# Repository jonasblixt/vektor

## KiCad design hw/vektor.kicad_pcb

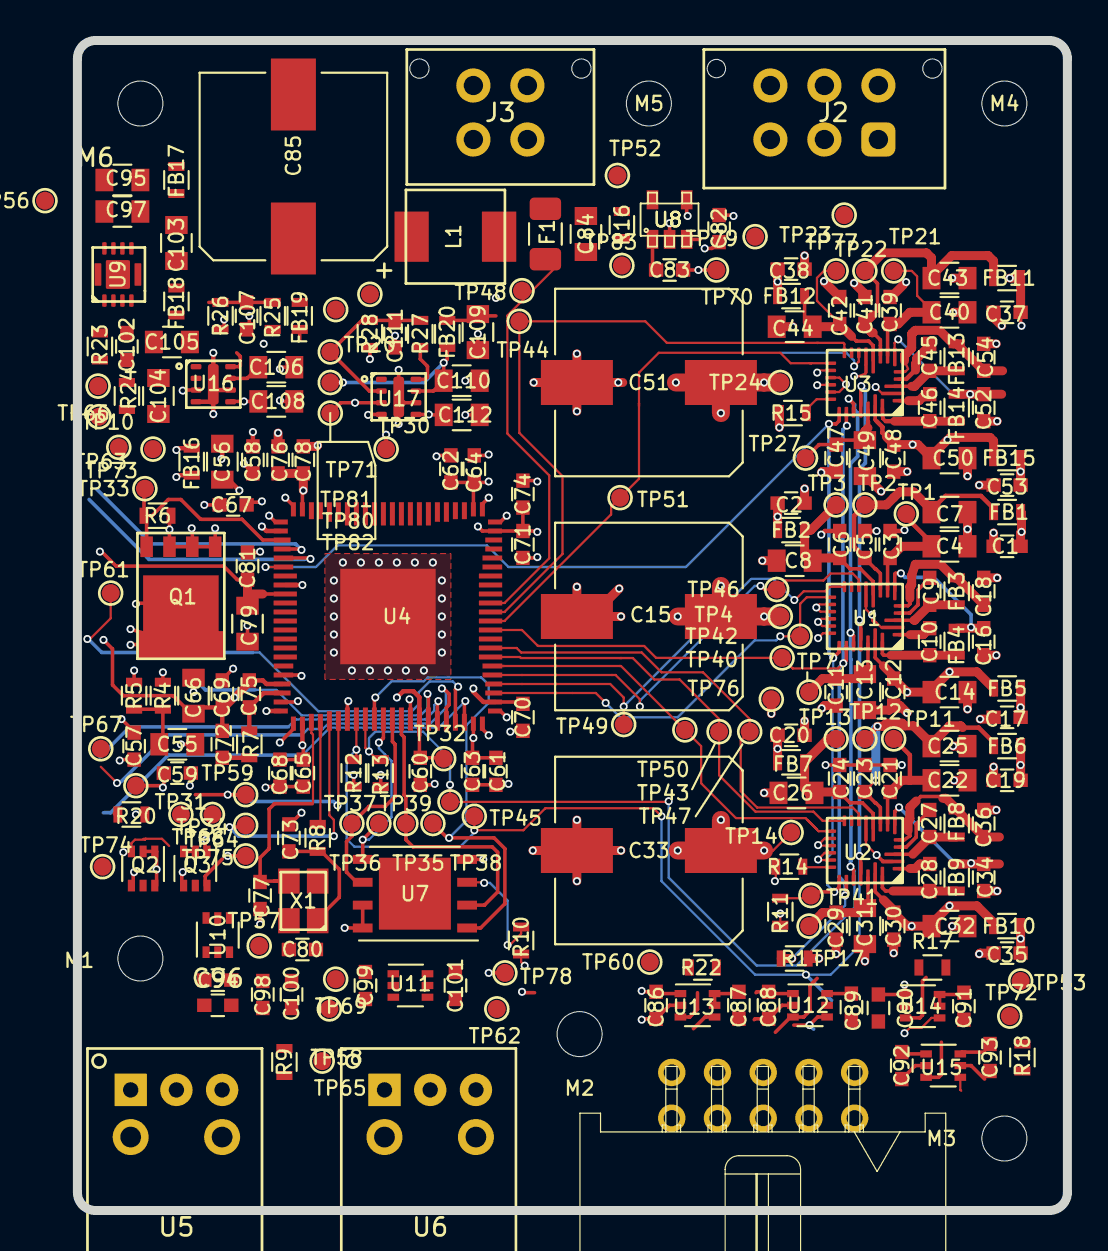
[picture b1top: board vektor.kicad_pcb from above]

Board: 6 copper layers, 55.0 x 65.0 mm, 257 parts (0 on the bottom side), 98 nets.

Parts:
C1, C2, C3, C5, C6, C9, C10, C11, C12, C17, C19, C20, C21, C23, C24, C27, C28, C29, C30, C35, C37, C38, C39, C41, C42, C45, C46, C47, C48, C53, C57, C58, C60, C62, C63, C64, C67, C68, C69, C70, C74, C78, C80, C82, C83: C0603_100n_50Vdc_X7R; C0603
C4, C7, C13, C22, C25, C31, C40, C43, C49: C0805_1u_50Vdc_X7R; C0805
C8, C14, C26, C32, C44, C50: C0805_10u_35Vdc_X5R; C0805
C15, C33, C51, C85: PCAP_120u_2; CP_Elec_10x10
C16, C18, C34, C36, C52, C54: C0603_1n2_50Vdc_C0G; C0603
C55, C56, C66, C79, C103, C104, C105, C106, C108, C109, C110, C112: C0805_10u_6.3Vdc_X7R; C0805
C59: C0603_10n_50Vdc_X7R; C0603
C61, C65, C71, C76, C81, C86, C87, C88, C89, C90, C91, C92, C93, C94, C96, C98, C99, C100, C101: C0603_1u_16Vdc_X7R; C0603
C72: C0603_5n6_25Vdc_C0G; C0603
C73, C77: C0603_22p_50Vdc_C0G_2; C0603
C75: C0603_150p_50Vdc_C0G_2; C0603
C84, C95: C0805_10u_25Vdc_X7R(Murata); C0805
C97: C0805_100n_25Vdc_X7R; C0805
C102: C0603_18p_100Vdc_C0G; C0603
C107, C111: C0603_470p_100Vdc_C0G; C0603
F1: 1206SFS200F_63-2; Fuse_1206_3216Metric
FB1, FB2, FB3, FB4, FB5, FB6, FB7, FB8, FB9, FB10, FB11, FB12, FB13, FB14, FB15, FB16: BL0603_BLM18EG121SN1D; L0603
FB17, FB18, FB19, FB20: BL0603_BLM18AG601SH1D; L0603
J1: TE_5103310-1; TE_5103310_1
J2: 430450629; Molex_430450629
J3: 430450427; Molex_430450427
L1: IHLP2020_4u7_31; IHLP2020
M1, M2, M3, M4, M5, M6: MHNP_2.5mm; MH_2.5mm
Q1: PHPT61002PYCLHX; PowerPAK_SO8
Q2: PUMH13; SOT-363_SC-70-6
Q3: PUMD13; SOT-363_SC-70-6
R1, R9, R10, R11, R16, R18, R20: R0603_10k; R0603
R4, R5: R0603_1R; R0603
R6: R0603_1k; R0603
R7: R0603_4k30; R0603
R8: R0603_100R; R0603
R12, R13: R0603_1k50; R0603
R14, R15: R0603_470R; R0603
R17, R22: R0603_100k; R0603
R23: R0603_680k; R0603
R24: R0603_120k; R0603
R25: R0603_118k; R0603
R26: R0603_150k; R0603
R27: R0603_187k; R0603
R28: R0603_82k50; R0603
TP1, TP2, TP3, TP4, TP7, TP10, TP11, TP12, TP13, TP14, TP17, TP20, TP21, TP22, TP23, TP24, TP27, TP30, TP31, TP32, TP33, TP34, TP35, TP36, TP37, TP38, TP39, TP40, TP41, TP42, TP43, TP44, TP45, TP46, TP47, TP48, TP49, TP50, TP51, TP52, TP53, TP56, TP57, TP58, TP59, TP60, TP61, TP62, TP63, TP64, TP65, TP66, TP67, TP68, TP69, TP70, TP71, TP72, TP73, TP74, TP75, TP76, TP77, TP78, TP79, TP80, TP81, TP82, TP83: TP; TP_1mm
U1, U2, U3: TAS2770; RJQ0026A
U4: ADAU1467; CP-88-10
U5: PLR135_T10
U6: PLT133_T10W
U7: 25AA1024; DFN-8-1EP_6x5mm_P1.27mm_EP4x4mm
U8: LP3470IM5X-3.08_NOPB; SOT-23-5
U9: XCL226A0K1H2; Torex_XCL22_QFN
U10, U11, U12, U13, U14, U15: 74LVCH1T45GW; SOT-363_SC-70-6
U16, U17: LMZ10501SILR; TI_LMX_SIL
X1: NX3225SA-12.288M-STD-CRS-2; NX3225SA

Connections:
/Amplifier 1/AMP_AREG: C11.1, C13.1, TP7.1, U1.24
/Amplifier 1/AMP_AVDD: C6.1, C8.1, FB2.2, TP3.1, U1.9
/Amplifier 1/AMP_DREG: C3.1, C4.1, TP1.1, U1.7
/Amplifier 1/AMP_IOVDD: C5.1, C7.1, FB1.2, TP2.1, U1.8
/Amplifier 1/AMP_OUT_N: C10.1, FB4.1, U1.26
/Amplifier 1/AMP_OUT_N_FLT: C16.1, FB4.2, J2.3, U1.6
/Amplifier 1/AMP_OUT_P: C9.1, FB3.1, U1.3
/Amplifier 1/AMP_OUT_P_FLT: C18.1, FB3.2, J2.4, U1.5
/Amplifier 1/FSYNC: TP42.1, U1.14, U4.47
/Amplifier 1/IRQ_N: R11.2, TP41.1, U1.20, U2.20, U3.20, U4.6
/Amplifier 1/P12V_AMP: C12.1, C14.1, C15.1, FB5.1, TP4.1, U1.25
/Amplifier 1/SCL: R12.2, TP45.1, U1.23, U2.23, U3.23, U4.30
/Amplifier 1/SDA: R13.2, TP39.1, U1.22, U2.22, U3.22, U4.31
/Amplifier 2/AMP_AREG: C29.1, C31.1, TP17.1, U2.24
/Amplifier 2/AMP_AVDD: C24.1, C26.1, FB7.2, TP13.1, U2.9
/Amplifier 2/AMP_DREG: C21.1, C22.1, TP11.1, U2.7
/Amplifier 2/AMP_IOVDD: C23.1, C25.1, FB6.2, TP12.1, U2.8
/Amplifier 2/AMP_OUT_N: C28.1, FB9.1, U2.26
/Amplifier 2/AMP_OUT_N_FLT: C34.1, FB9.2, J2.6, U2.6
/Amplifier 2/AMP_OUT_P: C27.1, FB8.1, U2.3
/Amplifier 2/AMP_OUT_P_FLT: C36.1, FB8.2, J2.2, U2.5
/Amplifier 2/FSYNC: TP50.1, U2.14, U4.50
/Amplifier 2/MODE: R14.2, U2.19
/Amplifier 2/P12V_AMP: C30.1, C32.1, C33.1, FB10.1, TP14.1, U2.25
/Amplifier 3/AMP_AREG: C47.1, C49.1, TP27.1, U3.24
/Amplifier 3/AMP_AVDD: C42.1, C44.1, FB12.2, TP23.1, U3.9
/Amplifier 3/AMP_DREG: C39.1, C40.1, TP21.1, U3.7
/Amplifier 3/AMP_IOVDD: C41.1, C43.1, FB11.2, TP22.1, U3.8
/Amplifier 3/AMP_OUT_N: C46.1, FB14.1, U3.26
/Amplifier 3/AMP_OUT_N_FLT: C52.1, FB14.2, J2.5, U3.6
/Amplifier 3/AMP_OUT_P: C45.1, FB13.1, U3.3
/Amplifier 3/AMP_OUT_P_FLT: C54.1, FB13.2, J2.1, U3.5
/Amplifier 3/FSYNC: TP51.1, U3.14, U4.55
/Amplifier 3/MODE: R15.2, U3.19
/Amplifier 3/P12V_AMP: C48.1, C50.1, C51.1, FB15.1, TP24.1, U3.25
/DSP/BCLK_OUT0: TP49.1, U1.13, U4.48
/DSP/BCLK_OUT1: TP43.1, U2.13, U4.51
/DSP/BCLK_OUT2: TP44.1, U3.13, U4.56
/DSP/EE_MISO: TP35.1, U4.35, U7.2
/DSP/EE_MOSI: TP37.1, U4.33, U7.5
/DSP/EE_SCLK: TP36.1, U4.34, U7.6
/DSP/EE_SS: R9.2, TP38.1, U4.32, U7.1
/DSP/MP7: R1.1, TP40.1, U1.21, U2.21, U3.21, U4.54
/DSP/P1V2_DVDD: C57.1, C59.1, C61.1, C63.1, C65.1, C68.1, C71.1, C74.1, C76.1, C78.1, Q1.5, R4.1, R5.1, TP31.1, U4.24, U4.43, U4.65, U4.87
/DSP/P1V8_IOVDD: C56.1, C58.1, C60.1, C62.1, C64.1, C67.1, C70.1, FB16.2, Q1.1, Q1.2, Q1.3, R6.2, TP32.1, U4.2, U4.22, U4.37, U4.46, U4.68
/DSP/PLLF: C75.2, R7.2, U4.20
/DSP/PLLF_2: C72.2, R7.1
/DSP/SDATA_OUT0: TP46.1, U1.11, U4.49
/DSP/SDATA_OUT1: TP47.1, U2.11, U4.52
/DSP/SDATA_OUT2: TP48.1, U3.11, U4.57
/DSP/VDRV: Q1.4, R6.1, TP33.1, U4.3
/IUSB_MISO: TP60.1, U4.38, U12.4
/IUSB_MISO_3V3: J1.8, R22.2, U12.3
/IUSB_MOSI: TP67.1, U4.40, U15.4
/IUSB_MOSI_3V3: J1.5, U15.3
/IUSB_RESET_N_3V3: J1.6, Q3.5
/IUSB_SCLK: TP62.1, U4.39, U14.4
/IUSB_SCLK_3V3: J1.7, R17.2, U14.3
/IUSB_SS_3V3: J1.9, R18.2, U13.3
/IUSB_SS_N: TP61.1, U4.41, U13.4
/P5V_FB: C102.2, R23.2, R24.1, TP63.1, U9.4
/P5V_LX: U9.1, U9.9
/P5V_OUT: C102.1, C103.1, FB18.1, R23.1, TP66.1, U9.10
/P12V_FLT_2: C95.1, C97.1, FB17.2, TP56.1, U9.6, U9.8
/RESET_N: Q3.6, R16.2, TP59.1, TP83.1, U4.28, U8.5
/SELFBOOT: Q2.3, R20.2, TP68.1, U4.42
/SPDIF_IN_1V8: TP64.1, U4.4, U10.4
/SPDIF_OUT_1V8: TP65.1, U4.5, U11.4
/VIN: C84.1, F1.2, L1.1, TP52.1
GND: C1.2, C2.2, C3.2, C4.2, C5.2, C6.2, C7.2, C8.2, C11.2, C12.2, C13.2, C14.2, C15.2, C16.2, C17.2, C18.2, C19.2, C20.2, C21.2, C22.2, C23.2, C24.2, C25.2, C26.2, C29.2, C30.2, C31.2, C32.2, C33.2, C34.2, C35.2, C36.2, C37.2, C38.2, C39.2, C40.2, C41.2, C42.2, C43.2, C44.2, C47.2, C48.2, C49.2, C50.2, C51.2, C52.2, C53.2, C54.2, C55.2, C56.2, C57.2, C58.2, C59.2, C60.2, C61.2, C62.2, C63.2, C64.2, C65.2, C66.2, C67.2, C68.2, C69.2, C70.2, C71.2, C73.2, C74.2, C76.2, C77.2, C78.2, C79.2, C80.2, C81.2, C82.2, C83.2, C84.2, C85.2, C86.2, C87.2, C88.2, C89.2, C90.2, C91.2, C92.2, C93.2, C94.2, C95.2, C96.2, C97.2, C98.2, C99.2, C100.2, C101.2, C103.2, C104.2, C105.2, C106.2, C107.2, C108.2, C109.2, C110.2, C111.2, C112.2, J1.10, J3.1, J3.2, Q2.1, Q2.2, Q2.4, Q2.6, Q3.1, R1.2, R14.1, R17.1, R22.1, R24.2, R26.2, R28.2, TP10.1, TP20.1, TP30.1, TP70.1, TP72.1, TP74.1, TP75.1, TP76.1, TP77.1, TP78.1, U1.2, U1.10, U1.15, U1.16, U1.17, U1.18, U1.19, U2.2, U2.10, U2.15, U2.16, U2.17, U2.18, U3.2, U3.10, U3.15, U3.16, U3.17, U3.18, U4.1, U4.8, U4.18, U4.21, U4.23, U4.29, U4.36, U4.44, U4.45, U4.66, U4.67, U4.88, U4.89, U5.2, U6.3, U7.4, U8.2, U9.2, U9.3, U9.11, U10.2, U11.2, U11.5, U12.2, U12.5, U13.2, U14.2, U15.2, U16.4, U16.6, U16.9, U17.4, U17.6, U17.9
unnamed: C9.2, U1.4
unnamed: C10.2, U1.1
unnamed: C27.2, U2.4
unnamed: C28.2, U2.1
unnamed: C45.2, U3.4
unnamed: C46.2, U3.1
unnamed: C55.1, R4.2, R5.2
unnamed: C73.1, R8.2, X1.1
unnamed: C77.1, U4.25, X1.3
unnamed: C83.1, U8.1
unnamed: C106.1, FB19.2, TP71.1, U16.7
unnamed: C107.1, R25.2, R26.1, TP73.1, U16.2
unnamed: C110.1, FB20.2, TP80.1, U17.7
unnamed: C111.1, R27.2, R28.1, TP81.1, U17.2
unnamed: F1.1, J3.3, J3.4
unnamed: J1.4, Q2.5
unnamed: Q3.2, Q3.3
unnamed: R8.1, U4.26
unnamed: R10.2, U7.3
unnamed: R25.1, U16.8
unnamed: R27.1, U17.8
unnamed: TP34.1, U4.27
unnamed: TP57.1, U5.3, U10.3
unnamed: TP58.1, U6.1, U11.3
P1V8: C1.1, C2.1, C19.1, C20.1, C37.1, C38.1, C80.1, C87.1, C89.1, C91.1, C93.1, C100.1, C101.1, C112.1, FB1.1, FB2.1, FB6.1, FB7.1, FB11.1, FB12.1, FB16.1, R9.1, R10.1, R11.1, R12.1, R13.1, R15.1, R16.1, R20.1, TP82.1, U7.7, U7.8, U10.6, U11.6, U12.6, U13.6, U14.6, U15.6, U17.3, U17.5
P3V3: C66.1, C69.1, C72.1, C75.1, C79.1, C81.1, C82.1, C86.1, C88.1, C90.1, C92.1, C108.1, Q3.4, R18.1, TP79.1, U4.9, U4.19, U8.3, U8.4, U12.1, U13.1, U13.5, U14.1, U14.5, U15.1, U15.5, U16.3, U16.5
P5V0: C94.1, C96.1, C98.1, C99.1, C104.1, C105.1, C109.1, FB18.2, FB19.1, FB20.1, TP69.1, U5.1, U6.2, U10.1, U10.5, U11.1
P12V: C17.1, C35.1, C53.1, C85.1, FB5.2, FB10.2, FB15.2, FB17.1, L1.2, TP53.1

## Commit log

2018-12-07 Initial hw structure
2019-07-11 Add pcb render
2019-07-31 Preparing R2
